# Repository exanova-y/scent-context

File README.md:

# nonhumanscent (prerelease)

MOX Array for ML-assisted Chemical Identification

Supports Bosch BSEC + AI-Studio

Made with atopile and kicad 9.

To Do:
- Test PCB
- Finish Bosch AI Studio Integration and BLE
- Add project page with calibration and usage documentation on my website
- Add store page for ordering assembled boards from moi

Created by lucy moglia <eigenlucy@proton.me>

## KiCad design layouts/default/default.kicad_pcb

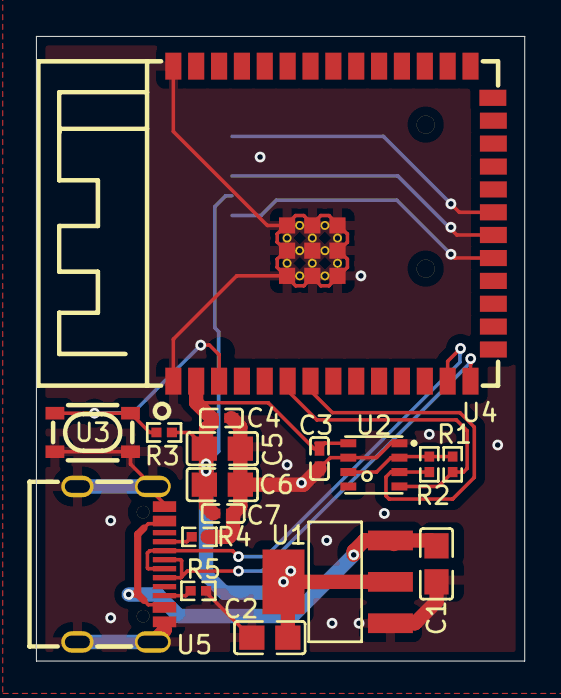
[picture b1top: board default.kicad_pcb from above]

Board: 2 copper layers, 27.1 x 34.7 mm, 18 parts (1 on the bottom side), 14 nets.

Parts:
C1, C2, C5, C6: 10µF ±10% 25V X5R; C0805-3b2e55
C3, C4, C7: 100nF ±10% 16V X7R; C0402-b3ef17
R1, R2: 1kΩ ±1% 62.5mW; R0402-56259e
R3: 10kΩ ±1% 62.5mW; R0402-56259e
R4, R5: 4.7kΩ ±1% 62.5mW; R0402-56259e
U1: SOT-223-3_L6.5-W3.4-P2.30-LS7.0-BR
U2: LGA-8_L3.0-W3.0-P0.80_BME688-7465bb
U3: KEY-SMD_4P-L4.2-W3.2-P2.20-LS4.6
U4: WIRELM-SMD_ESP32-S3-WROOM-1
U5: USB-C-SMD_KH-TYPE-C-16P
U6: TF-SMD_TF-01A

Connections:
A5: R4.1, U5.A5
CC2: R5.1, U5.B5
CLK_SCLK_: U4.20, U6.5
CMD_DI_: U4.19, U6.3
CSB: R1.2, R2.2, U2.2, U2.6
DAT0_D0_: U4.21, U6.7
SCK: R1.1, U2.4, U4.6
SDI: R2.1, U2.3, U4.7
gnd: C1.2, C2.2, C3.2, C4.2, C5.2, C6.2, C7.2, R4.2, R5.2, U1.1, U2.1, U2.7, U3.3, U3.4, U4.1, U4.40, U4.41, U5.1, U5.2, U5.3, U5.4, U5.A1, U5.A12, U5.B1, U5.B12, U6.6, U6.10, U6.11, U6.12, U6.13
hv: C2.1, C3.1, C4.1, C5.1, C6.1, C7.1, R3.1, U1.2, U1.4, U2.8, U4.2, U6.4
hv-1: C1.1, U1.3, U5.A4, U5.A9, U5.B4, U5.B9
in: R3.2, U3.1, U3.2, U4.3
io19: U4.13, U5.A7, U5.B7
io20: U4.14, U5.A6, U5.B6

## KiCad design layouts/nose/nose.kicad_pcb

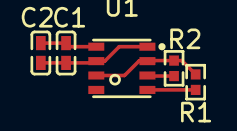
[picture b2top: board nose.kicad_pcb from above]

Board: 2 copper layers, 5 parts (0 on the bottom side), 5 nets.

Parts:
C1, C2: 100nF ±10% 16V X7R; C0402-b3ef17
R1, R2: 10kΩ ±1% 62.5mW; R0402-56259e
U1: LGA-8_L3.0-W3.0-P0.80_BME688-7465bb

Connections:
SCK: R1.1, U1.4
SDI: R2.1, U1.3
VDD: C1.1, C2.1, U1.8
VDDIO: R1.2, R2.2, U1.2, U1.6
gnd: C1.2, C2.2, U1.1, U1.7

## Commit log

2025-04-20 intial commit
2025-04-20 attached usb
2025-04-20 added firmware (configured for ESP32 rn for testing)
2025-04-24 finished PCB
2025-04-24 readme
2025-04-24 changed main build to app to fix build action
2025-04-24 fixed build list
2025-04-25 fixed power rails and added sd card
2025-04-25 fixed ato.yaml
2025-04-25 --no-frozen
2025-04-26 edited main.cpp to manually flash the config file from bosch AI studio, collected csv for 4 classes of scents for 5 mins each, created 5 plotly graphs
2025-04-26 new folder structure (push to exanova-y)
2025-04-26 added a dashboard and some fake data for the dashboard, that needs to be replaced with real data
2025-04-26 example scent vector search
2025-04-27 cleared up code
2025-04-27 add search bar
